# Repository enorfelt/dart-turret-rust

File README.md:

# dart-turret-rust

Rust firmware on ESP-IDF for the [Dart-Turret](https://www.printables.com/model/338574) Nerf turret (ESP32-S3), extended with autonomous targeting: an ESP32-S3 camera node for face detection and recognition, and a TFmini Plus lidar for range. See [docs/architecture.md](docs/architecture.md).

## Layout

```
crates/turret-core    no_std turret logic: SCS protocol, fire sequencer, command parser, BLE protocol codec
crates/turret-proto   no_std messages shared by all nodes (serde + postcard), host-tested
firmware/turret       ESP32-S3 turret controller (esp-idf-svc)
app/                  phone app: Angular PWA over Web Bluetooth
scripts/              WSL toolchain setup, Windows flashing helper
docs/                 architecture, safety rules, roadmap
```

## Setup (Windows + WSL Ubuntu)

Keep the clone in the WSL filesystem (e.g. `~/src/dart-turret-rust`); ESP-IDF builds on `/mnt/c` are very slow.

```sh
./scripts/setup-wsl.sh            # apt packages, rustup, espup (esp32s3 + esp32), espflash, ldproxy, Claude Code
./scripts/setup-wsl.sh --update   # update the same tools later
```

Open a new shell afterwards so `~/export-esp.sh` is sourced. Open the folder from VS Code or Cursor with the WSL remote extension so rust-analyzer runs inside WSL.

## Build

```sh
cargo test                                   # host crates, repo root
cd firmware/turret && cargo build            # first build downloads ESP-IDF v5.5 into ~/.espressif
```

The firmware build needs the 6-digit BLE pairing passkey in `TURRET_BLE_PASSKEY`. It is compiled in and never committed. Put it in your shell profile, e.g. `echo 'export TURRET_BLE_PASSKEY=123456' >> ~/.bashrc` with your own digits. Changing it requires `unpair` on the console and pairing the phone again.

## Phone app

The app in `app/` controls the turret from Chrome or Edge on Android or a desktop computer. Safari and Firefox have no Web Bluetooth.

The app uses Node 24 from nvm in WSL:

```sh
nvm install 24          # once
cd app && npm ci
npm start               # http://localhost:4200, open it in Windows Chrome
npm test -- --watch=false
```

Pushes to `main` that touch `app/` are deployed to GitHub Pages by `.github/workflows/app.yml`. This needs Pages enabled with "GitHub Actions" as the source. Open the Pages URL on the phone, connect, and enter the passkey when Android asks. Use "Add to Home screen" to install the app.

## Flash and monitor

### From Windows (recommended)

No USB passthrough needed. Requires espflash 4.x on Windows: `cargo +stable install espflash --locked`.

```powershell
pwsh -ExecutionPolicy Bypass -File \\wsl.localhost\Ubuntu\home\<user>\src\dart-turret-rust\scripts\flash.ps1 -Port COM4
```

`-ExecutionPolicy Bypass` is needed because `RemoteSigned` treats `\\wsl.localhost` paths as remote. The script only wraps `espflash flash --monitor --port COM4 <elf>`.

### From WSL

Attach the board with [usbipd-win](https://github.com/dorssel/usbipd-win) from Windows PowerShell (`bind` needs admin, once). `--auto-attach` matters on the ESP32-S3: its native USB re-enumerates when espflash resets it.

```powershell
usbipd list
usbipd bind --busid <BUSID>
usbipd attach --wsl --busid <BUSID> --auto-attach
```

```sh
cd firmware/turret && cargo run
```

If attach fails with `tcp connect` / "firewall appears to be blocking":

- Podman user-mode networking (`podman-net-usermode`) takes over the WSL default route, so usbipd connects to `192.168.127.1` instead of Windows. Pass the real host with `--host-ip <eth0 subnet>.1` (see `ip route` in WSL), or stop the Podman machine first.
- Windows Firewall must allow inbound TCP 3240 on the `vEthernet (WSL (Hyper-V firewall))` interface.

## Claude Code

`setup-wsl.sh` installs Claude Code natively in WSL. Run `claude` in the repo root and log in once. Project instructions are in `CLAUDE.md`; shared permissions in `.claude/settings.json`.

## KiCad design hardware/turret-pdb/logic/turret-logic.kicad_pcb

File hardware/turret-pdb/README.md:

# Turret controller boards

Two stacked two-layer KiCad 10 boards for the turret controller's low-current side. Ours are made by JLCPCB from the Gerbers that `export.sh` writes (see [Ordering from a fab](#ordering-from-a-fab)). The same design can also be [3D printed](#printed-boards), with the tracks made of copper wire laid in grooves or of copper tape.

- **Power board** (bottom): battery input, 12 V bench jack, the two input diodes, the three MP1584 bucks, the battery divider, the arm switch and pusher connections with the 1000 µF, and the servo bus and vision 5 V outputs. All the high-current nets stay on this board.
- **Logic board** (top): the ESP32-S3 in sockets, the level shifter, the light gate resistors and the connectors to the ESCs, TTLinker, TFmini Plus and light gate.

Five wires join the two boards. The ESCs stay on the quadcopter PDB; the power board takes one 20 AWG feed from a spare PDB pad pair.

Status: ERC and DRC clean on both boards, ordered from JLCPCB at 1.6 mm, not assembled yet. The module dimensions the footprints use are under [Module dimensions](#module-dimensions).

Both boards are 70 × 68 mm with 4 × M3 in the same places. The minimum track width is 2 mm, with 1 mm between tracks. The exceptions are pads and vias at 2.54 mm pitch, which need only 0.55 mm.

## Where it goes on the turret

The electronics sit between the two frame tubes (76 mm apart, inner edge to inner edge) behind the blue base that holds the batteries, in two stacks one behind the other. Nothing may rise above the top of the blue base, about 75 mm above the floor, because the turret sweeps that space.

```
        front (barrel)                                   rear
  ┌──────────────┐   ┌─────────────┐   ┌────────────────────┐
  │  blue base   │   │  Stack 1    │   │  Stack 2           │
  │  (battery)   │   │  PDB        │   │  logic board       │ ← ESP antenna at the rear edge
  │              │   │  BMS        │   │  power board       │
  └──────────────┘   └─────────────┘   └────────────────────┘
```

**Stack 1** holds bought boards:

| Layer | Part | Size | Mounting |
|---|---|---|---|
| Top | Quadcopter PDB (Matek PDB-XT60 clone), without its board XT60 | about 36 × 43 mm including the battery tab; 1.6 mm, flat underneath; parts up to about 4 mm tall | 4 × M3 on 30–30.5 mm, on the deck's pillars, battery tab pointing to the right-hand tube |
| Bottom | 4S 40 A BMS | 61 × 46 mm, about 5 mm thick; pads on the two 46 mm ends | No holes; on foam tape in the tray's pocket |

**Stack 2** is these two boards on four M3 standoffs: the power board at the bottom, the logic board on top, with the ESP's antenna end pointing to the rear.

Both stacks sit in the printed [stack tray](#stack-tray), which hangs under the tubes.

### Dimensions for the holders

Coordinates are in mm from the board's front-left corner, seen from the component side, with x across the tubes and y towards the rear. They come from `tools/stack.py`.

| What | Value |
|---|---|
| Outline | 70 (x, across the tubes) × 68 (y), 4 mm corner radius |
| M3 holes (3.2 mm) | (4, 4), (66, 4), (4, 64), (66, 64), the same on both boards |
| Board thickness | 1.6 mm for the JLCPCB boards; 2.0 mm for a printed board (one wired plate, or two 1.0 mm taped plates) |
| Gap between the boards | 17 mm, from the top of the power board to the bottom of the logic board |
| Stack 2 height | about 41 mm: pin tails under the power board, both boards, the gap and the ESP in its sockets |
| Link pads | x 37.1, at y 33, 39, 45, 51, 57 on both boards |
| ESP USB connector | logic board, front end of the ESP at about (37, 11); its plug points forwards, about 12 mm above the board |
| ESP antenna | logic board, rear edge between x 23 and 51; keep metal away from it |

The gap is set by the tallest part on the power board (C2, a 6.3 × 11 mm can standing on its leads, about 12.2 mm) plus the pin tails on the logic board's back (about 3 mm) plus 1 mm; `generate.py` checks it. Every power-board connection is a solder hole, because a plug mated to a header would not fit under the logic board.

## Stack tray

One printed tray holds both stacks and hangs under the two 12 mm frame tubes, with its floor 10 mm below them. Resting on the tubes, Stack 2 would rise about 10 mm above the 75 mm the turret sweeps. Its design is in `docs/superpowers/specs/2026-11-06-stack-tray-design.md`; every dimension is in `TRAY` at the top of `tools/tray.py`, and the Stack 2 holes come from `tools/stack.py`.

`tools/tray.py` checks the heights and the fit against the tubes, the BMS and Stack 2, and only then writes `out/tray/`:

| File | Print |
|---|---|
| `cradle-test.stl` | One cradle with a piece of floor. Print it first and try it on a tube offcut with two ties |
| `tray.stl` | The tray, 106 × 155 mm, floor down |
| `deck.stl` | The deck over the BMS, which carries the PDB, bar down |

Print in PLA with 0.2 mm layers, 4 walls and 40 % infill, without supports. The tubes rest in open cradles and zip ties over them carry the tray, so nothing has to flex. The tie tunnels through the cradles have pointed roofs, so nothing on the tray bridges.

| Hardware | Use |
|---|---|
| 4 × M3 × 16 with nuts | Up through the floor and the deck posts; the nut goes on top of the deck |
| 4 × M3 × 12 | Up through the floor and the power board into the bottom of Stack 2's 17 mm female–female standoffs |
| 4 × M3 × 8 with nuts | PDB to the deck pillars; the nuts slide into the slots near the pillar tops |
| M3 washers | Under every screw head and nut |
| 6 × 4.8 mm zip ties | Two per cradle, over the tubes |
| 3–4 small zip ties | Fuse holder and wires, through the tie slots in the floor |
| 3 small zip ties | Each XT60 pigtail's leads and the balance lead to the right-hand tube |
| 1 mm double-sided foam tape | Under the BMS |

1. Push the four deck-post screws up through the floor and the posts, each with a washer under its head.
2. Solder the pack, balance and output wires and the charger's JST-XH balance lead to the BMS, stick it into its pocket on foam tape, and tie the wires down through the slots next to its ends.
3. Lower the deck over the four post screws and fit a washer and nut on each. The BMS pad ends stay uncovered.
4. Leave the PDB's own XT60 off: standing upright on the tab, the battery plug on top of it would reach about 90 mm, into the turret's sweep. Solder a male XT60 pigtail (14 AWG, about 10 cm) to the tab's + and − pads instead. Slide an M3 nut into each pillar slot, then screw the PDB on with its tab pointing to the right. Route the fuse loop between the deck and the PDB and tie the fuse holder down in the gap between the stacks.
5. Build Stack 2 completely off the tray, as under [Assembly](#assembly), with female–female 17 mm standoffs: the link wires are soldered on the power board's back, which faces the floor once it is on the tray. Then stand it on the four bosses and drive the four M3 × 12 screws, with washers, up from under the floor into the standoffs.
6. Hold the tray up under the tubes, with Stack 1 towards the blue base, and fit two zip ties per cradle: in at the cradle's inner face, through the tunnel, up the outer face, over the tube and back.
7. Bring the PDB's male pigtail and the female pigtail from the fuse and BMS out past the right-hand tube, between the front and middle cradles, and zip-tie each one's leads to the tube so the connectors hang free just outside it. To switch off, hold one connector in each hand and pull them apart; the ties keep the pull off the solder pads. Tie the balance lead the same way, with its plug next to the female pigtail, for [charging](../../docs/wiring.md#charging).

PLA slowly gives way under constant pressure, so tighten the screws only until snug.

## Files

| Path | What |
|---|---|
| `power/`, `logic/` | One KiCad project per board: `turret-<board>.kicad_pro`, `.kicad_sch`, `.kicad_pcb`, `.kicad_dru`, and its own symbol and footprint library. Open the `.kicad_pro` in KiCad 10 |
| `tools/stack.py` | What both boards share: outline, M3 holes, the board gap, and the link pads with their net order |
| `tools/power.py`, `tools/logic.py` | Each board's parts, placement and every track |
| `tools/parts.py` | Footprints, with the module dimensions in `DIM` |
| `tools/generate.py` | Writes both projects from the files above and checks them: the logic board's ESP pins against `firmware/turret/src/board.rs`, the arm switch interlock nets, the link pads lining up on both boards with the same nets, nothing under the ESP antenna, nothing in the USB plug's path and C3 lying flat |
| `tools/route.py` | Maze router for a board's nets on both layers. It prints `T(...)`/`V(...)` lines to paste into that board's module after the tracks already there |
| `tools/board_shapes.py` | Runs in KiCad's bundled Python and writes the exact board outline, drill holes, copper polygons and track centre lines of both layers to `shapes.json` |
| `tools/plates.py` | Builds the plates to print from `shapes.json`: the wired plate, raised-track plates, and channel-method bases and companions. Every STL is checked to be watertight before it is kept, and the wired plate's grooves are checked for wall thickness between nets (needs `manifold3d`) |
| `tools/tray.py`, `tools/test_tray.py` | The [stack tray](#stack-tray) and its tests |
| `tools/export.sh` | Runs ERC and DRC and writes `out/<board>/` for each board: the print plates, a one-piece `preview.stl`, copper PDFs to use as a cutting guide, an assembly PDF, renders, and Gerbers and drill files for a fab in `gerbers/` and `turret-<board>-gerbers.zip` |

```sh
cd hardware/turret-pdb
python3 tools/generate.py           # both boards; only while the design lives in tools/, see below
tools/export.sh                     # both boards, or name one: tools/export.sh logic
python3 tools/route.py power GND    # route one or more nets of a board; GND alone takes under a minute
tools/export.sh tray                # only the stack tray, into out/tray/
cd tools && .venv/bin/python -m unittest test_tray   # the stack tray's tests
```

`export.sh` needs KiCad 10 on Windows; set `KICAD_CLI` to use another kicad-cli. For the print plates, it uses `tools/.venv`:

```sh
python3 -m venv tools/.venv && tools/.venv/bin/pip install manifold3d numpy
```

`generate.py` overwrites the schematics and the boards. Once you start editing in KiCad, stop running it, or carry your edits back into `tools/` first.

## Layout

On both boards every part is soldered on the back only. Front copper never connects to a pad; it reaches the parts through vias, with a short back-side track from each via to its pad. A DRC rule ("Parts are soldered on the back only") flags any front track that touches a pad, including after edits in the KiCad GUI.

**Power board.** The three bucks stand in a row across the front, outputs forwards, so each output is a short track to its connector on the front edge: J11 (7.5 V), J3 (arm switch, 6 V) and J10 (5 V). Wires to the arm switch (J3), the vision node (J10) and the pusher (J4) have no tie hole on the board; strain-relieve them on the holder. VIN runs as a 4 mm front-layer track under the modules from via to via, and the pusher's switched 6 V runs on the front from J3 down to J4 and C3, so signals and GND can cross both on the back. The diodes, the jack and the battery input sit at the rear right, the divider's 39 kΩ next to the battery input. 13 vias: 5 GND, 3 VIN, 3 PUSH_6V, 2 for 5 V.

**Logic board.** The ESP runs front to rear with its antenna at the rear edge and nothing under the antenna. The link pads and the level shifter sit between the two socket rows, under the Freenove board, which stands about 11 mm up on its sockets; the shifter is about 5.5 mm tall. Each shifter pin faces the ESP pin it connects to. The ESC, TTLinker and TFmini connectors are on the right; the light gate connector and its two resistors are on the left, next to GPIO 42. 5 V reaches the TFmini and the link pad on a front-layer track down the right side, and 3V3 runs on the front from the ESP's 3V3 pin to the shifter and the light gate. 14 vias: 5 GND, 3 for 3V3, 2 each for 5 V, PUSH_SIG and ARM_SENSE.

Next to an ESP pin, a track runs either straight out or into the gap between the two header rows. Two 2 mm tracks never enter neighbouring 2.54 mm pins from the same side.

## Module dimensions

The footprints use these dimensions, and the ordered boards were made with them.

| Check | Where | Value used |
|---|---|---|
| MP1584 hole spacing, IN+ to OUT+ and IN+ to IN−, measured on your modules | `DIM["mp1584_pad_dx"]`, `["mp1584_pad_dy"]` | 19.0 × 14.0 mm, measured |
| Distance between the two Freenove header rows | `DIM["esp_row_spacing"]` | 25.4 mm, measured |
| Adafruit 757 row spacing | `DIM["shifter_row_spacing"]` | 10.16 mm, from Adafruit's EAGLE board |
| Length of the 1000 µF body, lying on its side | `DIM["c3_length"]` | 20 mm (10 × 20 mm can) |
| Clear height under the Freenove board between its header rows, with it plugged into the sockets | — | at least 6 mm for the shifter, measured |

If a value changes, run `generate.py`. The routes move with the pads, so run `export.sh` again and fix anything DRC reports in `tools/power.py` or `tools/logic.py`. The boards already ordered then no longer match.

## Ordering from a fab

Ours are from JLCPCB. `export.sh` writes each board's Gerbers (both copper layers, mask, silkscreen and outline, Protel file names, no X2) and Excellon drill files (mm, plated and unplated holes in separate files) into `out/<board>/gerbers/`, and zips them as `out/<board>/turret-<board>-gerbers.zip`. Upload the zip to JLCPCB or PCBWay as it is; both read these settings.

| Option | Value |
|---|---|
| Layers | 2 |
| Size | 70.1 × 68.1 mm, the same for both boards |
| Thickness | 1.6 mm, as ordered, and the cheapest. The board file says 2.0 mm only because that is the printed plate; the Gerbers do not carry it. Header pins stick out about 1.4 mm on the back |
| Smallest hole | 1.0 mm plated; the M3 holes are 3.2 mm unplated |
| Copper | 1 oz is enough; the 5 V and VIN tracks are 2–4 mm wide |

## Assembly

1. **Vias.** On the fab boards every pad and via is plated, so there is nothing to do. On a printed board, push 0.8 mm bare copper wire through each via, solder it on both sides, and trim it flush; with the wire method this is already done.
2. **Parts.** Fit every part from the front and solder it on the back, like a single-sided board. That covers the resistors, capacitors, diodes, jack, headers and wires.
3. **MP1584 modules.** Mount them on ordinary male header pins with the plastic spacer in place, soldered on the back. Set each output before connecting anything, then lock the trimmer with a drop of glue. The MG996R is damaged above 7.2 V.
4. **1000 µF (C3).** Bend its leads 90° so it lies flat on the power board, body towards the board's left edge, as drawn on the assembly PDF. Standing up it would hit the logic board.
5. **Level shifter.** The Adafruit 757 mounts **upside down**: solder its two 6-pin headers on the component side of the breakout, so the parts face the board. The footprint is mirrored to match. Its A3/B3 and LV-side GND pins have bare holes only. Trim the header pins that stick up above the breakout, so it stays under 6 mm.
6. **ESP sockets.** Use two full 1×20 female strips. First pull the metal contacts out of every position the board has no hole for, marked x on the assembly PDF: grip each contact's tail with pliers and push it out. Then solder the remaining contacts on the back. The empty positions keep the strip in one piece without touching the tracks that run under it.
7. **Stack.** The link tracks run on the back of both boards. The J12 holes on the fab boards are plated, so a link wire works soldered on either face; on a printed board they are not, so each wire must be soldered on the back face of both boards. Cut five wires about 35 mm long: 22 AWG for GND and 5V, 26 AWG for VBAT, ARM and PUSH. Push each into the logic board's J12 from the back and solder it on the back; the pad names are on the assembly PDF, seen from the front. Bolt the power board onto four M3 standoffs so its top face and the logic board's bottom face are 17 mm apart. Lower the logic board onto the standoffs, threading each wire down through the power board's J12 hole with the same name, and solder them on the power board's back. J12 sits between the ESP sockets, so do this before plugging in the ESP.

## Connectors

Pin 1 is the square pad.

**Power board**

| Ref | Function | Pins |
|---|---|---|
| J1 | Battery in (from a PDB pad pair, 20 AWG) | 1 VBAT, 2 GND, solder holes |
| J2 | 12 V bench adapter, 5.5 × 2.1 mm, centre positive | |
| J3 | Arm switch (DPST) | 1 6V switched (to pusher), 2 6V, 3 GND, 4 SENSE (GPIO 47), solder holes. Pole A goes on 1–2 and pole B on 3–4. This still works with the switch wired the other way round |
| J4 | Pusher servo | 1 GND, 2 6V switched, 3 signal (5 V), solder holes. Cut the servo plug off, or solder a short pigtail with a plug in line |
| J10 | Vision node 5V | 1 5V, 2 GND, solder holes |
| J11 | Servo bus power to TTLinker VIN | 1 7.5V, 2 GND, solder holes |
| J12 | Link to the logic board | 1 GND, 2 5V, 3 VBAT (divided), 4 ARM, 5 PUSH, solder holes |

**Logic board**

| Ref | Function | Pins |
|---|---|---|
| J5, J6 | ESC left, right | 1 GND, 2 not connected (leave the BEC red wire free), 3 signal |
| J7 | Feetech TTLinker logic side | 1 5V, 2 GND, 3 TTLinker TXD, 4 TTLinker RXD. Swap 3 and 4 if `ping 0` gets no answer |
| J8 | TFmini Plus | 1 5V, 2 GND, 3 TFmini TX, 4 TFmini RX |
| J9 | Light gate | 1 IR LED anode (cathode to 3), 2 phototransistor collector, 3 GND (LED cathode and phototransistor emitter) |
| J12 | Link to the power board | as on the power board |

## Differences from the loose wiring in `docs/wiring.md`

- **Level shifter channels:** A1/B1 is GPIO 14 → TTLinker RXD, A2/B2 the pusher, and A4/B4 TTLinker TXD → GPIO 21. A3/B3 is unused. The firmware is unchanged.
- **Light gate LED:** it runs from 3V3 through 150 Ω (about 13 mA) instead of 5 V through 330 Ω, since 3V3 is closer to the gate connector.
- **Divider and capacitors:** the battery divider sits on the power board at the battery input, before D1. Only the divided voltage goes up to the logic board. The 1000 µF sits at the pusher connector.
- **Diode OR on the input:** two SB560 Schottky diodes feed the bucks from either the battery or the 12 V jack, so neither source can back-feed the other. The divider measures the battery only. On the jack alone it reads under 5 V ("no pack"), the same as on USB.
- **7.5 V rail:** the 7.5 V servo rail is an MP1584, rated 3 A peak. Two stalled SC15s draw 3.4 A, so a double stall can make it overheat and cut out.

## Bench mode (12 V jack)

- With only the jack plugged in, the bucks, ESP, gimbal and pusher have power, but the ESCs on the PDB do not.
- Arming works as it does on USB, so the pusher can be exercised without flywheels.
- A 12 V 2.5 A adapter covers normal servo tests, but not a stall of both SC15s plus the pusher.
- Unplug both the jack and the battery before plugging in USB, as with the XT60.
- After assembly, check that J1 reads about 0 V with only the jack plugged in. That shows nothing back-feeds the PDB.

## Safety checks after assembly

- With the arm switch open, there must be no continuity from +6V (J3 pin 2) to the pusher V+ (J4 pin 2). `PUSH_6V` only reaches J3 pin 1, J4 pin 2 and the 1000 µF, all on the power board; `generate.py` checks this.
- The ESC middle pins have no copper.
- Check the five link wires with a meter through the joints, not on the J12 pads: GND from J10 pin 2 (power) to J7 pin 2 (logic), 5V from J10 pin 1 to J7 pin 1, and the other three from the power board part to the ESP socket contact (VBAT: R2 to GPIO 1, ARM: J3 pin 4 to GPIO 47, PUSH: J4 pin 3 to the shifter's B2). Do this before plugging in the ESP.
- Set and lock the buck outputs before the ESP, servos or sensors are plugged in.

## Printed boards

The alternative to a fab, for building a board the same day. The process is new, so print a small piece first: cut the ESP header area out of the logic board's model in Bambu Studio, then tape and solder a few pins. The [module dimensions](#module-dimensions) apply to printed boards too.

### Printing

`export.sh` writes three ways of building each board into `out/power/` and `out/logic/`: the [wire method](#wire-method), which is one plate with no tape, and two copper tape methods. The finished board is 2.0 mm thick whichever you choose, so 2.54 mm header pins and part leads still stick out about 1 mm on the back.

For the tape methods, every plate is ready to print flat side down and tracks up, and the back plates are already mirrored. Each plate is 1.0 mm thick: a 0.6 mm base with 0.4 mm raised copper.

| File (per board) | Plate |
|---|---|
| `front-raised.stl` | Front (component side) |
| `back-raised.stl` | Back (solder side) |
| `preview.stl` | The whole board as one 2.0 mm solid, for checking that the two faces line up. Not for printing |

1. Import both plates of a board into Bambu Studio and print them side by side. After printing they line up on the four M3 holes.
2. Optionally cut a small piece out with the Cut tool to try the process first.
3. Print in one of the [materials](#material) below. Use 0.2 mm layers, 4 walls, 100 % infill and ironing on the top surface, so the tape has a smooth surface to stick to.
4. Printed holes come out small. Drill them to size by hand: 1.2 mm for pins and leads, 1.0 mm for vias, 1.7 mm for the diodes and 1.6 mm for the wire holes.

#### Material

PLA is fine for a turret used indoors. In normal use the plate stays well under PLA's softening point of about 55 °C. The wire tracks barely warm up, and the bucks stand on their pins above the board. Only the SB560 diodes get hot, and only during long servo stalls. PETG or ASA take more heat and are more forgiving to solder on, so use one of them if the turret may stand in the sun or in a hot car.

PLA softens under the iron, so with PLA:

- Solder quickly with plenty of flux, and pre-tin wire ends before joining them. The wire method's 0.8 mm wire draws far more heat into the plastic than tape does, and only the plastic holds it in its groove.
- Let a joint cool before soldering the one next to it. Hold the wires with tweezers where they meet until the solder sets.
- Do not overtighten the M3 screws. PLA slowly gives way under constant pressure; use washers.
- After a stall test or a long burst, touch the plate near D1 and D2. It should be comfortable to hold.

### Copper tape

Tape each plate on its own, before joining them.

1. **Back plate (tracks).** Lay the tape over the tracks and press it onto the raised surface with a fingernail or a spudger. Cut along each track edge with a fresh blade, then peel the tape off the low areas. `back-copper-mirrored.pdf` shows the pattern as seen from the back.
2. **Front plate.** Do the same with `front-copper.pdf` as the guide. Both faces have only tracks and pads, so no wide areas need covering.
3. Where a track is wider than one strip, or two strips overlap at a bend, solder the seam. Copper tape adhesive does not conduct well.
4. Bolt the plates together with the M3 screws, with a thin layer of glue between them if you like, and open the holes through the tape.
5. Tin the power tracks on the power board (VIN, the battery input, the 12 V jack, 7.5 V, 6 V and the pusher's switched 6 V) with a layer of solder. Tape is only 35–50 µm thick.

### Channel method (no knife trimming)

`export.sh` also writes a second set of parts for the method used by PCB Forge. The copper sits in 0.4 mm channels, and each channel is outlined by a narrow ridge. You sand the ridges, which cuts the tape around every trace, so no knife work is needed.

| File (per board) | Print | Use |
|---|---|---|
| `front-base.stl`, `back-base.stl` | Channels up | The two board plates: 1.0 mm thick, 0.4 mm deep channels where the copper goes, and a 0.6 mm wide, 0.4 mm tall ridge around each channel. The back one is already mirrored |
| `front-companion.stl`, `back-companion.stl` | Bosses up | Press plates. Their bosses are the copper shapes, mirrored and inset by 0.15 mm, so they drop 0.3 mm into the channels when the plate is laid face down. Pockets around the bosses clear the ridges |

1. Print the bases and companions in one of the [materials](#material), with no XY compensation.
2. Cover a base with copper tape. Lay its companion face down on top, line it up on the M3 holes, and press hard, or clamp it, so the tape is forced into every channel.
3. Remove the companion and sand only the ridges, with sandpaper on a flat block, until the plastic shows along every ridge. That cuts the tape around each trace; the tape in the channels stays.
4. The tape left on the flat areas between ridges is now isolated from the traces. Peel it off, or leave it if it is stuck down well; it connects to nothing.
5. Wipe off the dust with isopropyl alcohol, check with a meter that neighbouring tracks are isolated, then carry on from step 4 of [Copper tape](#copper-tape) and with [Assembly](#assembly) as for the raised-track version.

Seams still need soldering where two strips meet in a channel.

### Wire method

The tracks are 0.75–0.8 mm tinned copper bus wire (about 20 AWG), pressed into grooves in a single printed plate. There is no tape, no knife work and no second plate to line up. The wire carries more current than any of the tape tracks, so the power tracks need no tinning.

`wired.stl` is the whole board as one 2.0 mm plate, already turned back face up for printing. Both faces have 1.0 mm wide, 0.6 mm deep grooves along the track centre lines. The grooves continue from where a track meets a pad into the pad's hole, and each hole has a solder well 0.4 mm wider than the hole. The back has wells at every hole, the front at the vias only, since no part is soldered on the front. `plates.py` stops if two nets' grooves, wells or holes come closer than 0.4 mm, and prints how much wire each face needs.

1. Print in one of the [materials](#material) as exported, back face up, with 0.2 mm layers, 100 % infill, the Arachne wall generator and no ironing. The front grooves are on the bed side; they bridge over 1 mm and need no supports. Set elephant foot compensation to about 0.15 mm so they do not close up.
2. Drill the holes as for the tape plates. Vias need 1.0 mm for the wire.
3. **Front.** Straighten the wire by pulling it. Lay it into one groove at a time, bending it at the corners with pliers, and press it in with the iron at about 200 °C for PLA or 250 °C for PETG and ASA, so it sinks into the plastic and stays. At a via, push the wire through the hole and leave a few millimetres on the back.
4. **Back.** Do the same. Bend each via tail from the front into the back groove that leaves that via, or solder it to that groove's wire in the well.
5. At a pad, stop the wire at the edge of the hole. The part's lead and the wire are soldered together in the well.
6. Solder every place where two wires meet. Check with a meter that neighbouring tracks are isolated, then carry on with [Assembly](#assembly) from step 2. The vias are already done.

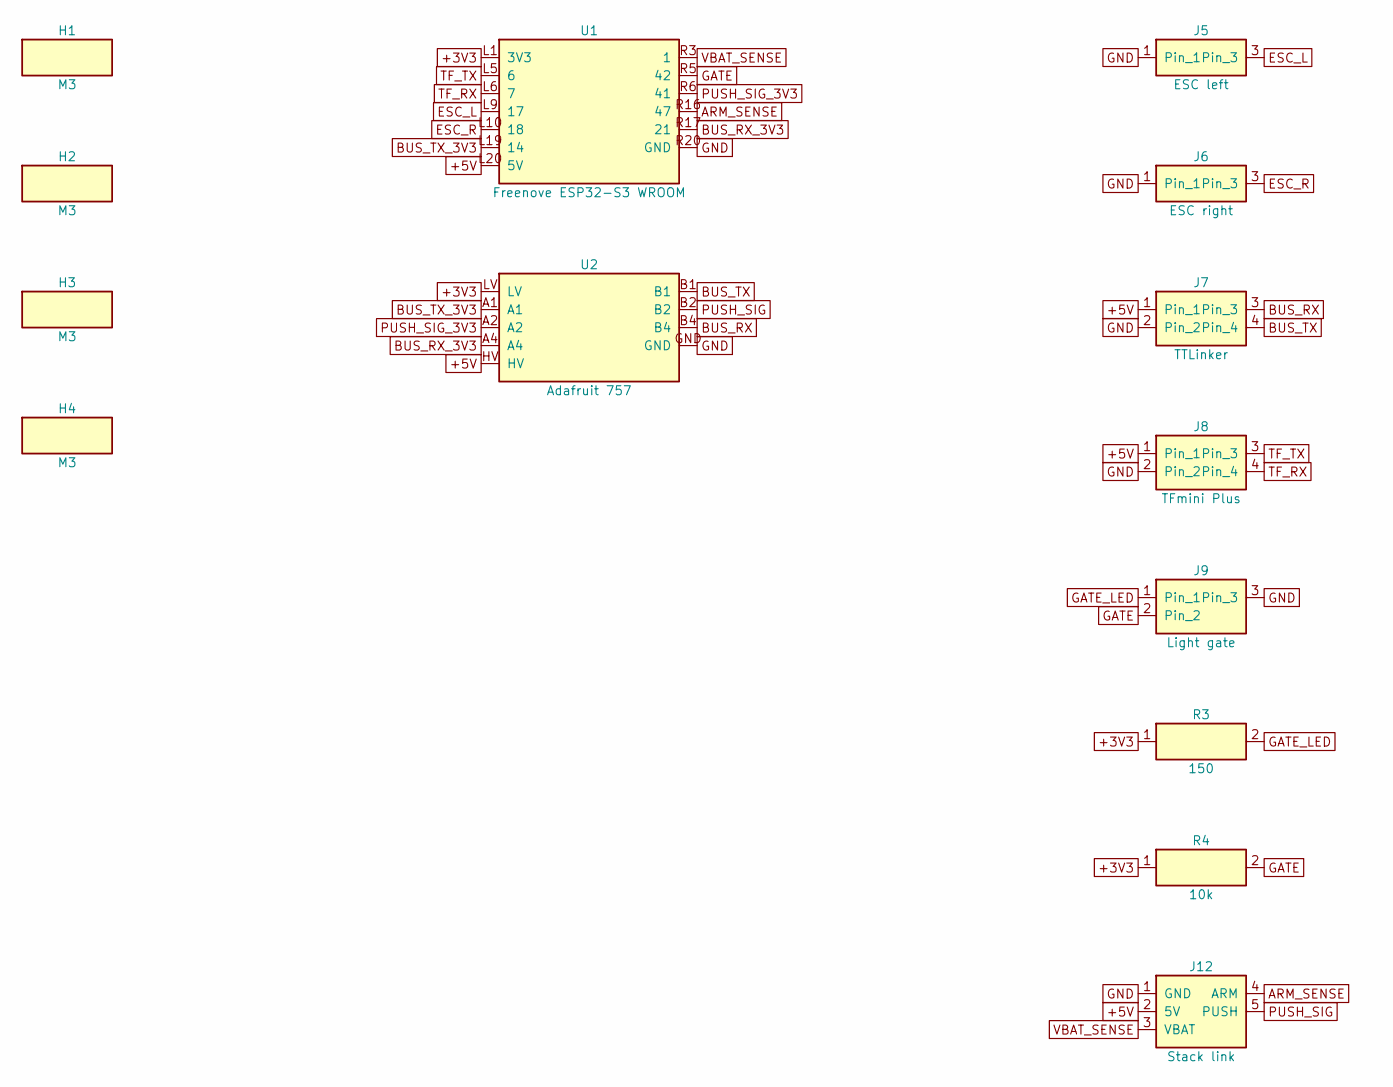
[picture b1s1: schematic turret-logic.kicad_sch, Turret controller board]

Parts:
H1, H2, H3, H4: M3; MountingHole_M3
J5: ESC left; PinHeader_1x03_P2.54mm_ESC
J6: ESC right; PinHeader_1x03_P2.54mm_ESC
J7: TTLinker; PinHeader_1x04_P2.54mm
J8: TFmini Plus; PinHeader_1x04_P2.54mm
J9: Light gate; PinHeader_1x03_P2.54mm
J12: Stack link; WirePads_1x05_NoTie
R3: 150; R_Axial_P10.16mm_Horizontal
R4: 10k; R_Axial_P10.16mm_Horizontal
U1: Freenove ESP32-S3 WROOM; Freenove_ESP32-S3_WROOM_Socket
U2: Adafruit 757; Adafruit_757_UpsideDown

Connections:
+3V3: R3.1, R4.1, U1.L1 (3V3), U2.LV
+5V: J7.1, J8.1, J12.2 (5V), U1.L20 (5V), U2.HV
ARM_SENSE: J12.4 (ARM), U1.R16 (47)
BUS_RX: J7.3, U2.B4
BUS_RX_3V3: U1.R17 (21), U2.A4
BUS_TX: J7.4, U2.B1
BUS_TX_3V3: U1.L19 (14), U2.A1
ESC_L: J5.3, U1.L9 (17)
ESC_R: J6.3, U1.L10 (18)
GATE: J9.2, R4.2, U1.R5 (42)
GATE_LED: J9.1, R3.2
GND: J5.1, J6.1, J7.2, J8.2, J9.3, J12.1 (GND), U1.R20 (GND), U2.GND
PUSH_SIG: J12.5 (PUSH), U2.B2
PUSH_SIG_3V3: U1.R6 (41), U2.A2
TF_RX: J8.4, U1.L6 (7)
TF_TX: J8.3, U1.L5 (6)
VBAT_SENSE: J12.3 (VBAT), U1.R3 (1)

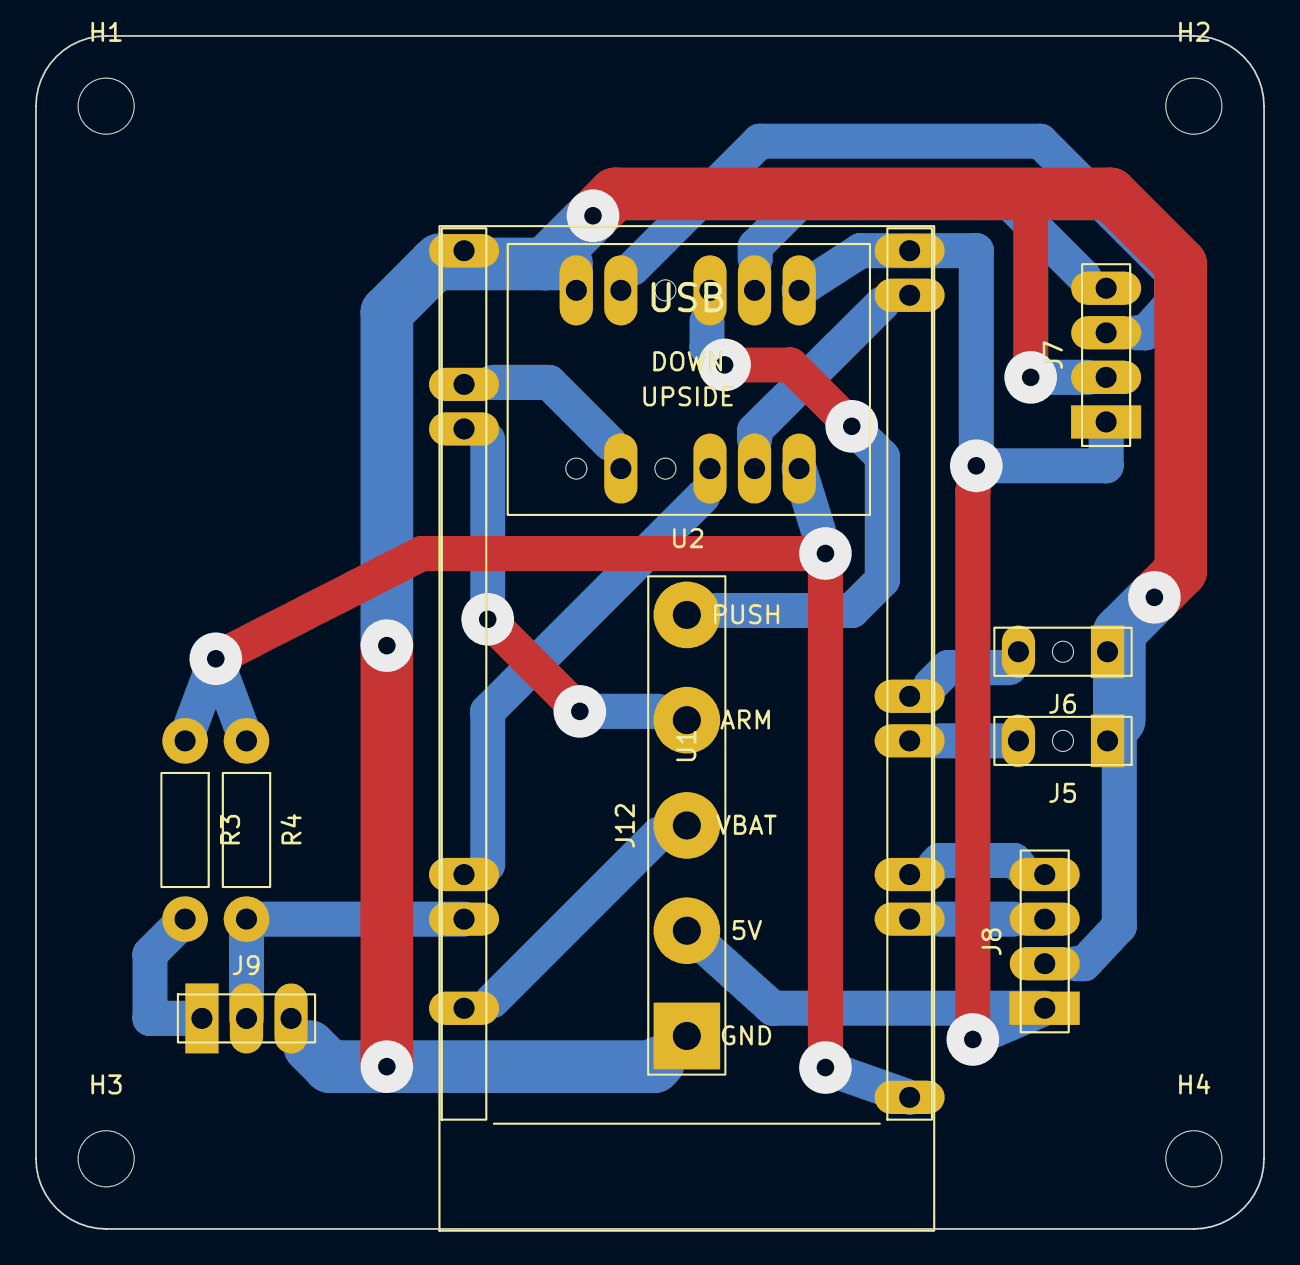
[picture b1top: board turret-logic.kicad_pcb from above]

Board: 2 copper layers, 70.0 x 68.0 mm, 14 parts (0 on the bottom side), 17 nets.

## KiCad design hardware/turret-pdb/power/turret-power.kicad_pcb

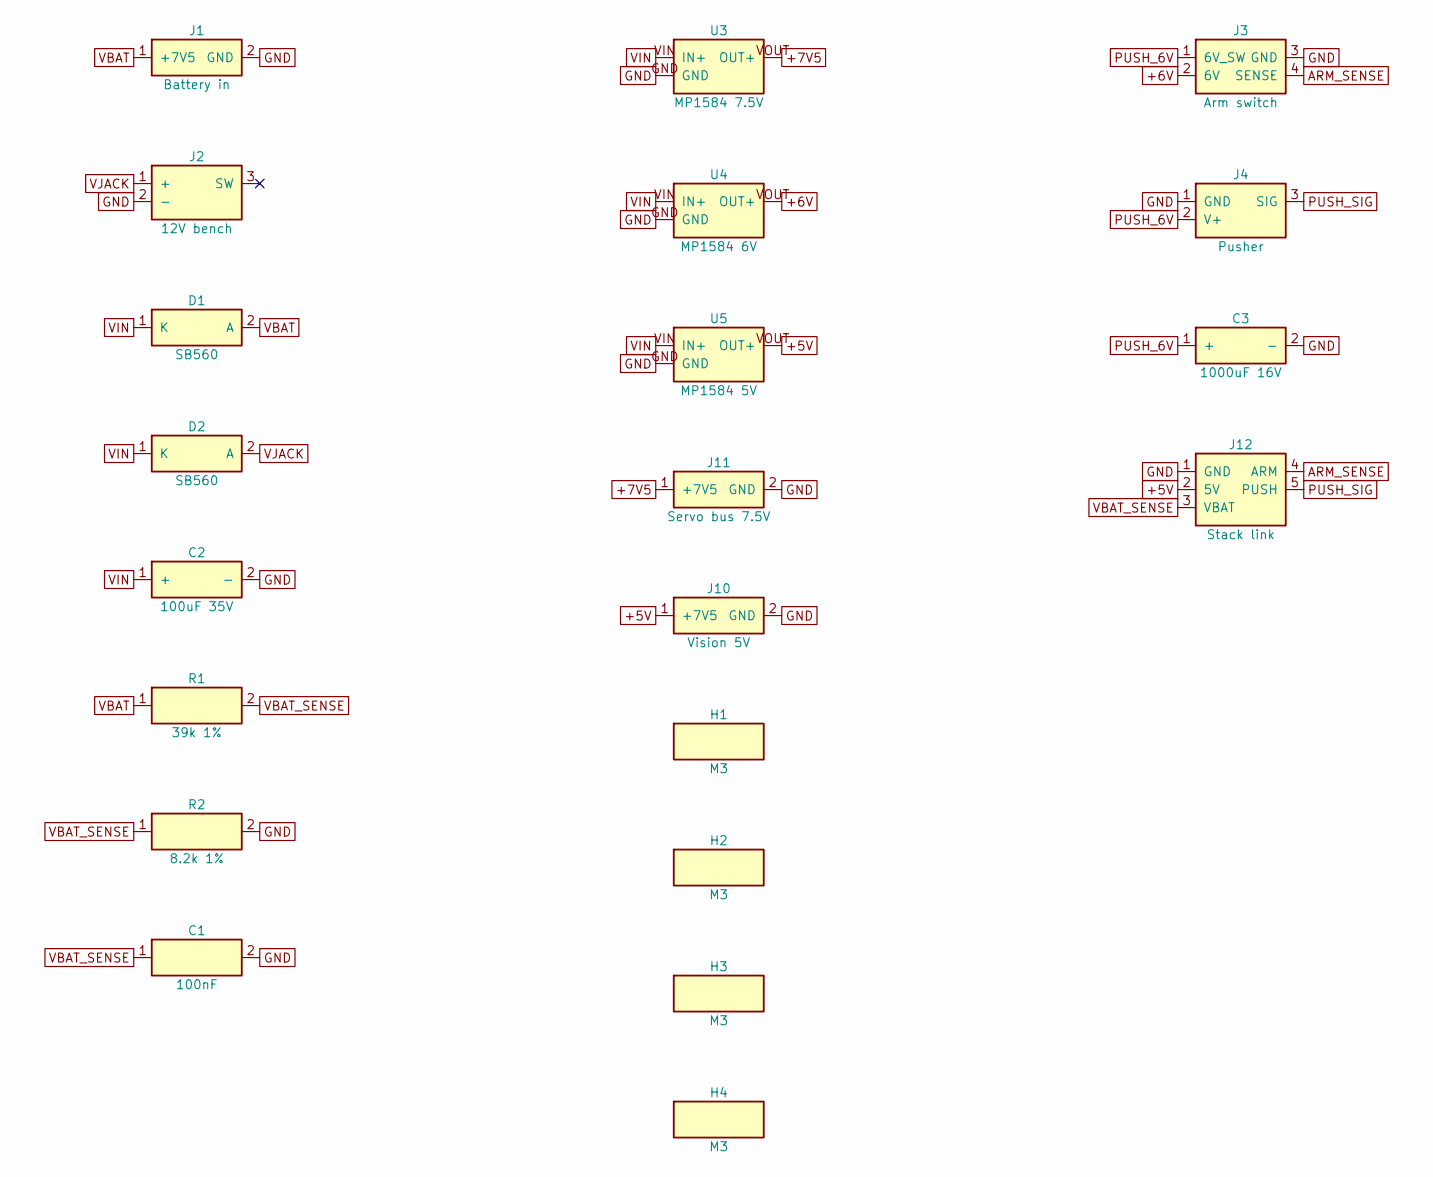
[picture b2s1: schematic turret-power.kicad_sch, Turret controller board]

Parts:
C1: 100nF; C_Disc_P5.00mm
C2: 100uF 35V; CP_Radial_D6.3mm_P2.50mm
C3: 1000uF 16V; CP_Radial_D10.0mm_L20.0mm_P5.00mm_Lying
D1, D2: SB560; D_DO-201AD_P12.70mm_Horizontal
H1, H2, H3, H4: M3; MountingHole_M3
J1: Battery in; WirePads_1x02_TieLeft
J2: 12V bench; BarrelJack_5.5x2.1_Horizontal
J3: Arm switch; WirePads_1x04_NoTie
J4: Pusher; WirePads_1x03_NoTie
J10: Vision 5V; WirePads_1x02_NoTie
J11: Servo bus 7.5V; WirePads_1x02_TieRight
J12: Stack link; WirePads_1x05_NoTie
R1: 39k 1%; R_Axial_P10.16mm_Horizontal
R2: 8.2k 1%; R_Axial_P10.16mm_Horizontal
U3: MP1584 7.5V; MP1584_Module
U4: MP1584 6V; MP1584_Module
U5: MP1584 5V; MP1584_Module

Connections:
+5V: J10.1 (+7V5), J12.2 (5V), U5.VOUT (OUT+)
+6V: J3.2 (6V), U4.VOUT (OUT+)
+7V5: J11.1 (+7V5), U3.VOUT (OUT+)
ARM_SENSE: J3.4 (SENSE), J12.4 (ARM)
GND: C1.2, C2.2 (-), C3.2 (-), J1.2 (GND), J2.2 (-), J3.3 (GND), J4.1 (GND), J10.2 (GND), J11.2 (GND), J12.1 (GND), R2.2, U3.GND, U4.GND, U5.GND
PUSH_6V: C3.1 (+), J3.1 (6V_SW), J4.2 (V+)
PUSH_SIG: J4.3 (SIG), J12.5 (PUSH)
VBAT: D1.2 (A), J1.1 (+7V5), R1.1
VBAT_SENSE: C1.1, J12.3 (VBAT), R1.2, R2.1
VIN: C2.1 (+), D1.1 (K), D2.1 (K), U3.VIN (IN+), U4.VIN (IN+), U5.VIN (IN+)
VJACK: D2.2 (A), J2.1 (+)

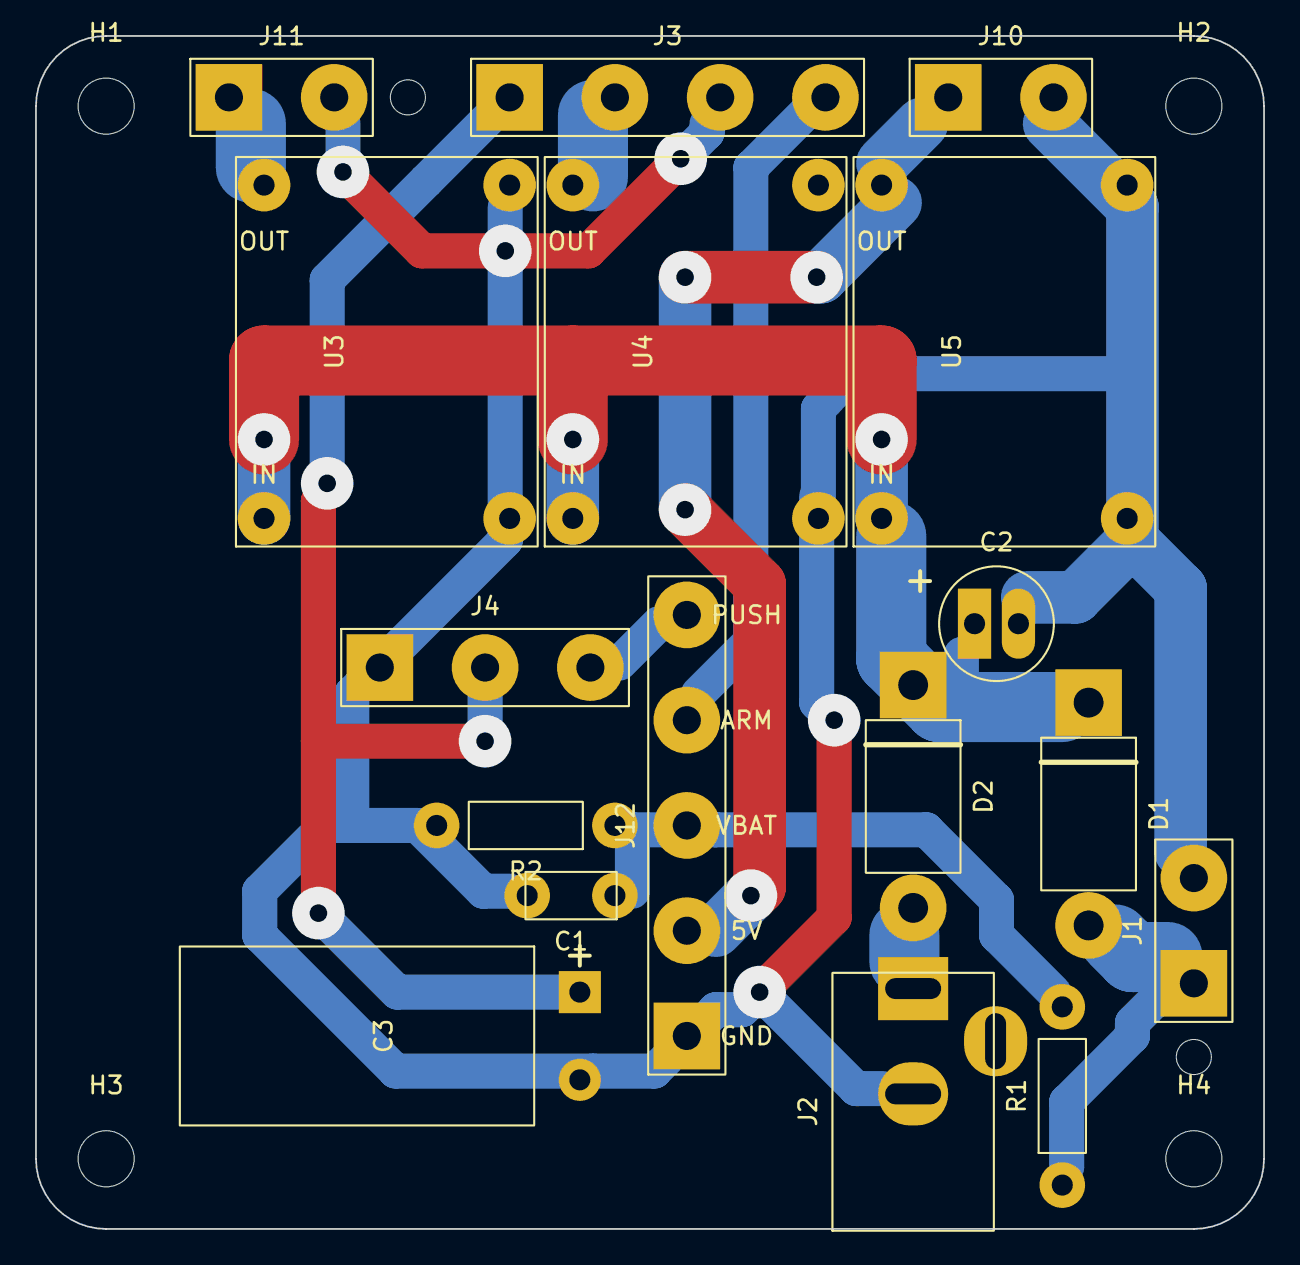
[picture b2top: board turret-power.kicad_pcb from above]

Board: 2 copper layers, 70.0 x 68.0 mm, 21 parts (0 on the bottom side), 11 nets.
